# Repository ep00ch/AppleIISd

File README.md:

# This Fork
This fork of AppleIISd is designed to use a Motorola MC6852 Synchronous Serial Communications Adapter rather than the specified Xilinix CPLD. 
The MC6852 IC is expected to produce an SPI compatible signal, though only at 1 MHz speeds. The project uses the 
[SparkFun Level Shifting microSD Breakout](https://www.sparkfun.com/products/13743) to handle the voltage level shifting problem.
This is an untested work in progrees.

# AppleIISd
SD card based ProFile replacement for enhanced Apple IIe and IIgs computers

The **AppleIISd** is a SD card based replaced for the ProFile harddrive. In contrast to other SD card based devices, this card does not replace a Disk II drive. Data is saved directly onto the SD card, not via images on a FAT system, like on other cards. The SD card is accessable with [CiderPress](http://a2ciderpress.com/).

A Xilinx CPLD is used as a SPI controller and translates, together with the ROM driver, SD card data to/from the Apple IIe. The VHDL source is based on [SPI65/B](http://www.6502.org/users/andre/spi65b) by André Fachat.

The assembler sources are written for CC65. The [schematics](AppleIISd.pdf) are available as PDF.

## Features
* works with ProDOS and GS/OS
* up to 128MB storage space (4x 65535 blocks)
* ProDOS and Smartport driver in ROM
* Auto boot
* Access LED
* Card detect and write protect sensing
* Skip boot when Open-Apple key is pressed

## Requirements
The AppleIISd requires an enhanced IIe or IIgs computer. The ROM code uses some 65c02 opcodes and will therefore not work on a II, II+ or unenhanced IIe. It has been tested in the following combinations:
* Apple IIgs Rom 01, GS/OS 6.0.4
* Apple IIgs Rom 01, Prodos 2.4.1
* Apple IIgs Rom 01, Prodos 1.9
* Apple IIe enhanced, 128k, Prodos 2.4.1
* Apple IIe enhanced, 128k, Prodos 1.9
* Apple IIe enhanced, 64k, Prodos 1.9

When a 2732 type ROM is used, the binary image has to be programmed at offset 0x800, because A11 is always high for compatibility with 2716 type ROMs.

## Smartport drive remapping
The AppleIISd features Smartport drivers in ROM to provide more than two drives in both GS/OS and ProDOS.

As ProDOS supports only two drives per slot, additional drives on a Smartport device are mapped to 'phantom slots'. Version prior to version 2 supported only the remapping of drives when the card was in slot 5. Starting with version 2, the remapping seems to work on all slots. The following list shows the assignments as slot/drive, when no other devices are attached:

* Slot 7: 7/1, 7/2, 4/1, 4/2
* Slot 6: 6/1, 6/2, 4/1, 4/1
* Slot 5: 5/1, 5/2, 2/1, 2/1
* Slot 4: 4/1, 4/2, 1/1, 1/2
* Slot 3: 80 col HW, not usable
* Slot 2: 2/1, 2/2, 4/1, 4/2
* Slot 1: 1/1, 1/2, 4/1, 4/2

When more devices are connected, things get a little confusing ;-)

## Building the sources
Be sure to have the newest version of CC65 (V2.16) and some kind of Make instaled, then type one of the following comands:
```
make                            # generate binaries
make OPTIONS=mapfile,listing    # generate mapfile and listing, too
make clean                      # delete binaries
```
Alternatively use the VisualStudio solution.

## Timing
The clock of the SPI bus *SCK* may be derived from either *Phi0* or the *7M* clock. Additionally, the divisor may be 2 to 8.

The following measurements were taken with the divisor set to 2, resulting in *fSCK* of 500kHz and 3.5MHz. Reading of a byte requires that a dummy byte is sent on the bus, before the answer can be read. Therefore the measurement is the time between sending the byte and receiving the answer. The measurement for reading of a whole 512 byte block includes the SD card commands to do so.

| Clock  | Byte   | Block  | Image                                             |
| -----: | -----: | -----: | ------------------------------------------------: |
| *Phi0* | 17.7µs | 28.8ms | [Byte](Images/Bus1.gif), [Block](Images/Spi1.png) |
| *7M*   | 3.9µs  | 15ms   | [Byte](Images/Bus2.gif), [Block](Images/Spi2.png) |

This shows that the required to read a single byte can be reduced significantly by increasing *fSCK* (as one might have guessed). Reading at 500kHz actualy requires NOPs to be inserted (or checking the TC bit in the STATUS register), while reading at 3.5MHz can be done immediately.

The time for reading a 512 byte block could *only* be halved, but there are for sure opportunities for optimization in the code surrounding the reading.

```
* single byte @ 500kHz
LDA #$FF
STA $C0C0
NOP
NOP
NOP
NOP
NOP
NOP
NOP
LDA $C0C0

* single byte @ 3.5MHz
LDA #$FF
STA $C0C0
LDA $C0C0
```

## TODOs
* Much more testing
* SRAM option (may never work, though)
* Enable more than 4 volumes under GS/OS
* Use 28 pin socket to support other EPROMS than 2716 and 2732

## Known Bugs
* Does not work with some Z80 cards present

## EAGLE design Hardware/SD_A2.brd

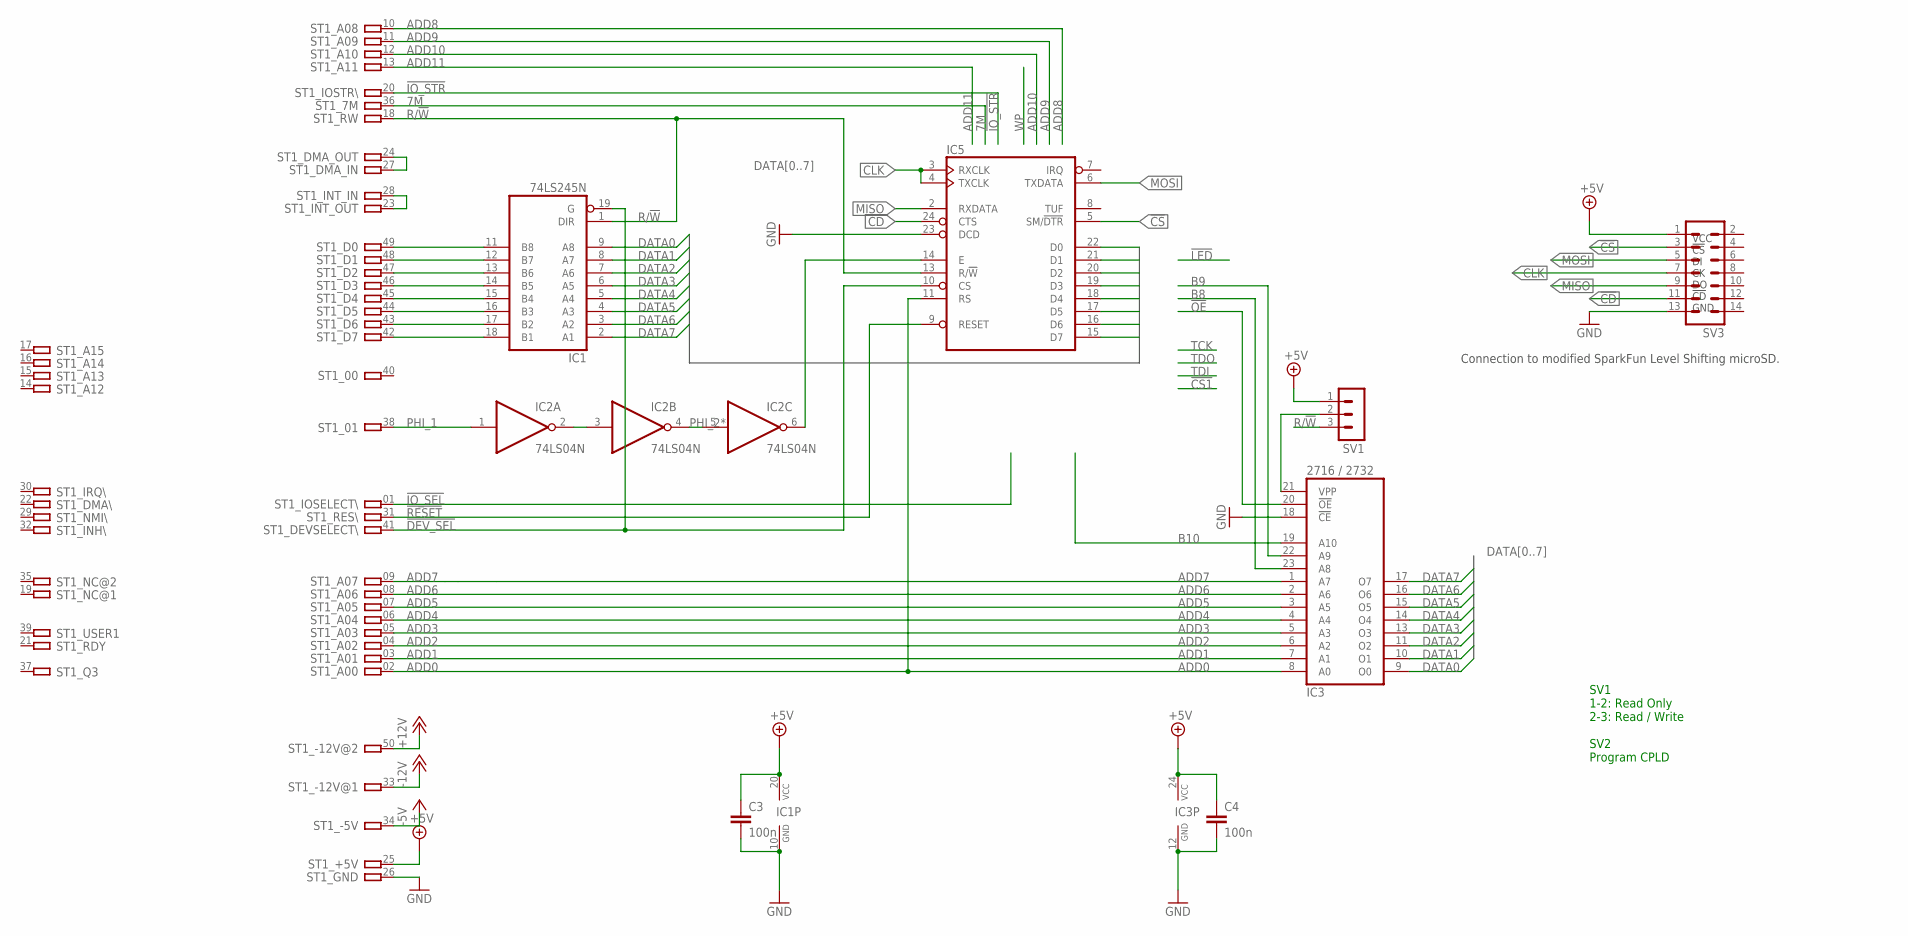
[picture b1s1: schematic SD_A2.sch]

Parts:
C3, C4: 100n; C0603K
IC1: 74LS245N; DIL20
IC2: 74LS04N; DIL14
IC3: 2716 / 2732; DIL24
IC5: 6852; DIL24
ST1: A2-50PINSLOT1-3; A2-50PIN-SL1-3
SV1: MA03-1
SV3: MA07-2

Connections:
7M: ST1.36
!CD: IC5.24 (CTS), SV3.11
!CS: IC5.5 (SM/!DTR), SV3.3
!DEV_SEL: IC1.19 (G), IC5.10 (CS), ST1.41
!IO_SEL: ST1.01
!IO_STR: ST1.20
!OE: IC3.20 (!OE)
!RESET: IC5.9 (RESET), ST1.31
+5V: C3.1, C4.1, IC1.20 (VCC), IC3.24 (VCC), ST1.25, SV1.1, SV3.1
+12V: ST1.50
-5V: ST1.34
-12V: ST1.33
ADD0: IC3.8 (A0), IC5.11 (RS), ST1.02
ADD1: IC3.7 (A1), ST1.03
ADD2: IC3.6 (A2), ST1.04
ADD3: IC3.5 (A3), ST1.05
ADD4: IC3.4 (A4), ST1.06
ADD5: IC3.3 (A5), ST1.07
ADD6: IC3.2 (A6), ST1.08
ADD7: IC3.1 (A7), ST1.09
ADD8: ST1.10
ADD9: ST1.11
ADD10: ST1.12
ADD11: ST1.13
B8: IC3.23 (A8)
B9: IC3.22 (A9)
B10: IC3.19 (A10)
CLK: IC5.3 (RXCLK), IC5.4 (TXCLK), SV3.7
DATA0: IC1.9 (A8), IC3.9 (O0), IC5.22 (D0)
DATA1: IC1.8 (A7), IC3.10 (O1), IC5.21 (D1)
DATA2: IC1.7 (A6), IC3.11 (O2), IC5.20 (D2)
DATA3: IC1.6 (A5), IC3.13 (O3), IC5.19 (D3)
DATA4: IC1.5 (A4), IC3.14 (O4), IC5.18 (D4)
DATA5: IC1.4 (A3), IC3.15 (O5), IC5.17 (D5)
DATA6: IC1.3 (A2), IC3.16 (O6), IC5.16 (D6)
DATA7: IC1.2 (A1), IC3.17 (O7), IC5.15 (D7)
GND: C3.2, C4.2, IC1.10 (GND), IC2.7 (GND), IC3.12 (GND), IC3.18 (!CE), IC5.23 (DCD), ST1.26, SV3.13
MISO: IC5.2 (RXDATA), SV3.9
MOSI: IC5.6 (TXDATA), SV3.5
unnamed: IC2.2 (O), IC2.3 (I)
unnamed: IC2.4 (O), IC2.5 (I)
unnamed: ST1.24, ST1.27
unnamed: ST1.23, ST1.28
unnamed: IC1.11 (B8), ST1.49
unnamed: IC1.18 (B1), ST1.42
unnamed: IC1.17 (B2), ST1.43
unnamed: IC1.16 (B3), ST1.44
unnamed: IC1.15 (B4), ST1.45
unnamed: IC1.14 (B5), ST1.46
unnamed: IC1.13 (B6), ST1.47
unnamed: IC1.12 (B7), ST1.48
PHI_1: IC2.1 (I), ST1.38
PHI_2*: IC2.6 (O), IC5.14 (E)
R/!W: IC1.1 (DIR), IC5.13 (R/!W), ST1.18, SV1.3
VCC: IC2.14 (VCC), IC5.12 (VCC)
VPP: IC3.21 (VPP), SV1.2
VSS: IC5.1 (VSS)

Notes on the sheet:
SV1 1-2: Read Only 2-3: Read / Write SV2 Program CPLD
VCC !CS DI CK DO !CD GND
Connection to modified SparkFun Level Shifting microSD.

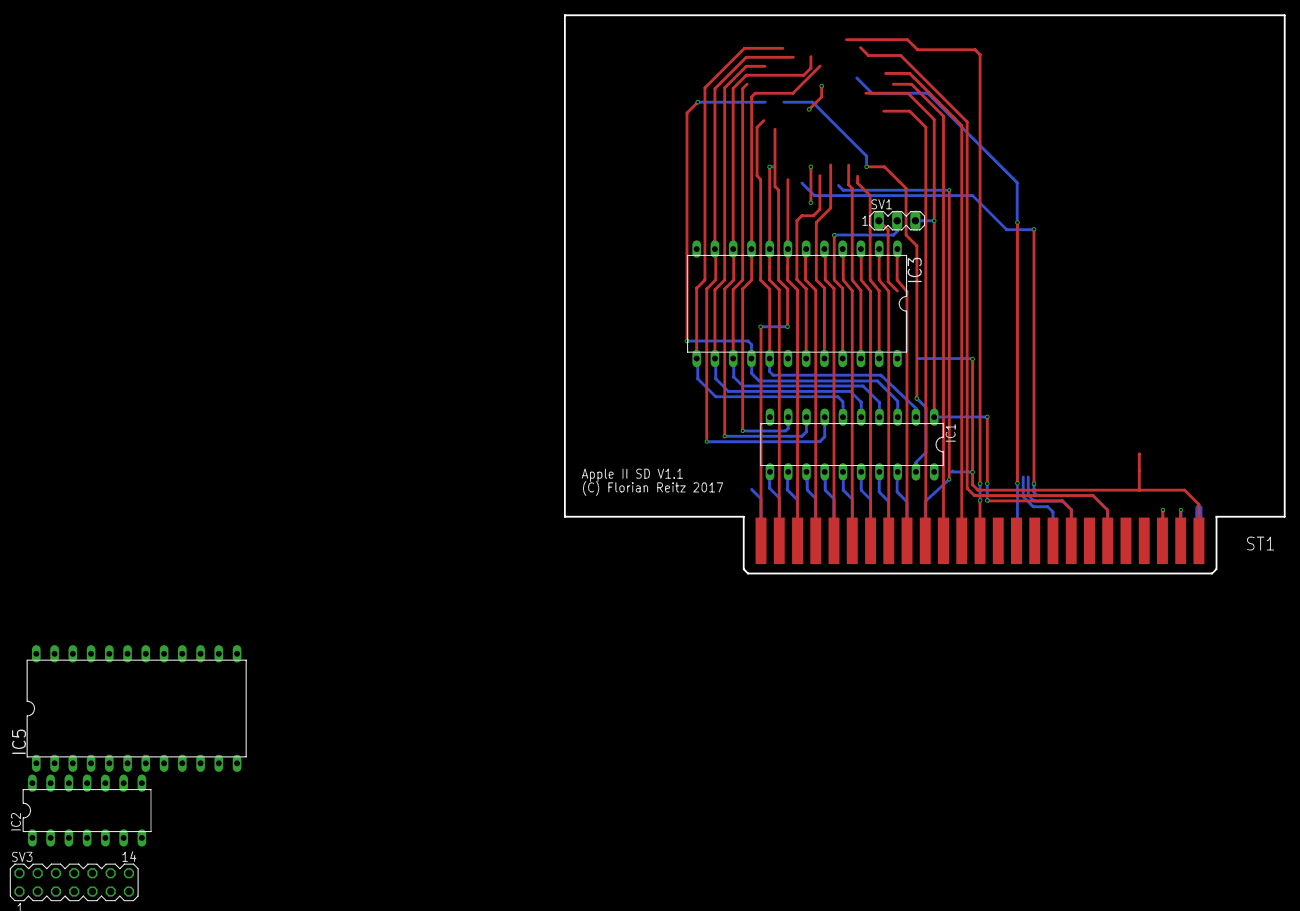
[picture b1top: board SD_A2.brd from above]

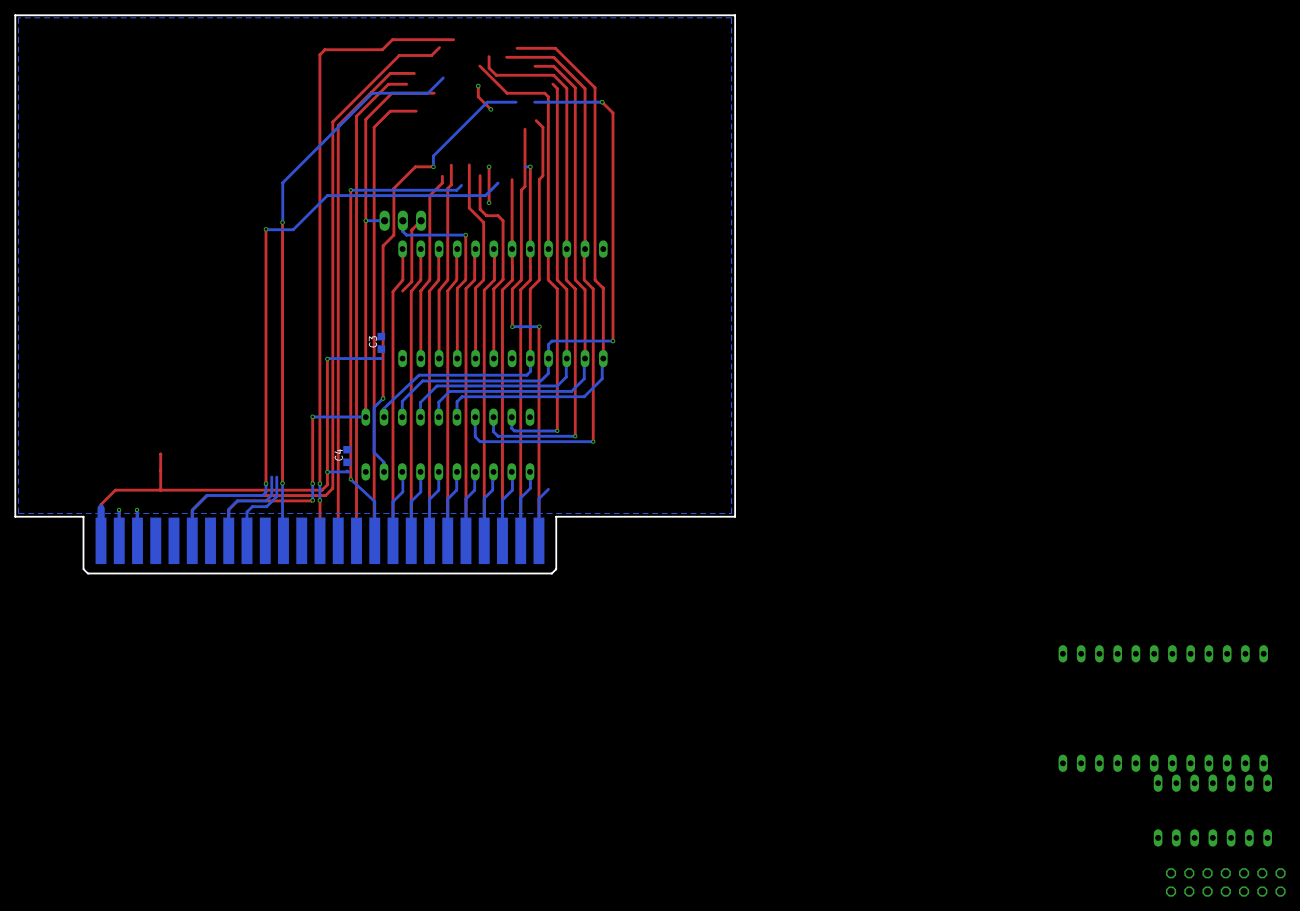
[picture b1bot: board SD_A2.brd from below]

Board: 2 copper layers, 100.2 x 77.7 mm, 9 parts (2 on the bottom side), 42 nets.

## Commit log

2019-04-15 Replace CPLD with MC6852 and add Level Shifting microSD Breakout.
2019-04-26 updated datasheets with searchable text Please enter the commit message for your changes. Lines starting
2019-04-26 Added include with MC6852 SSD register definitions
